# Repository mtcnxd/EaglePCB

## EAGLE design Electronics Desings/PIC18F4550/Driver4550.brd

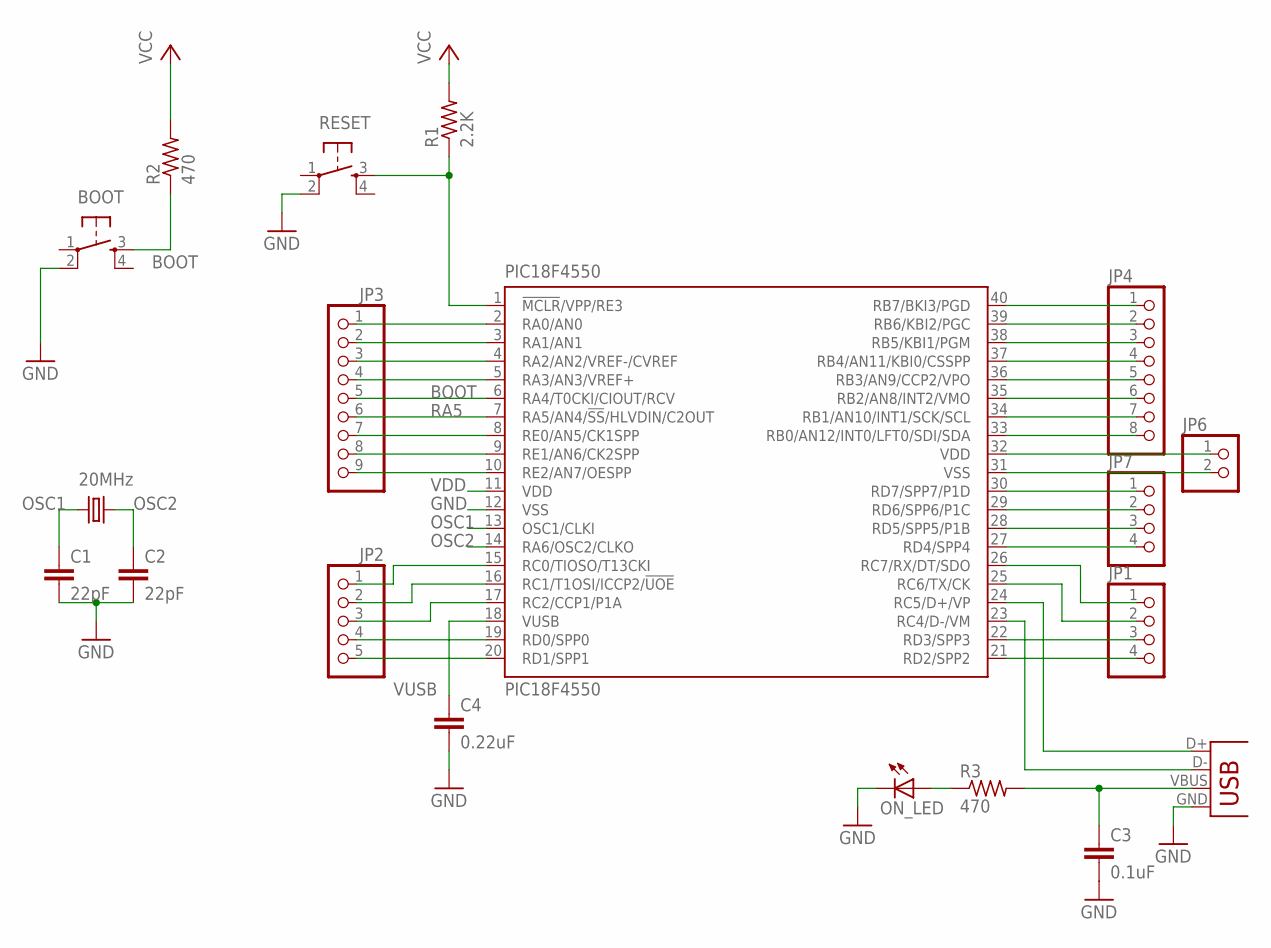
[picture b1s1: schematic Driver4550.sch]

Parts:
BOOT: TAC_SWITCHPTH; TACTILE-PTH
C1, C2: 22pF; C5B3
C3: 0.1uF; C2.5-3
C4: 0.22uF; C5B3
CRYSTAL: 20MHz; HC49US
JP1, JP7: PINHD-1X4; 1X04
JP2: PINHD-1X5; 1X05
JP3: PINHD-1X9; 1X09
JP4: PINHD-1X8; 1X08
JP6: PINHD-1X2; 1X02
ON_LED: LED3MM
PIC18F4550: PIC18F4550; DIL40
R1: 2.2K; 0204/7
R2, R3: 470; 0204/7
RESET: TAC_SWITCHPTH; TACTILE-PTH
USB: X1; USB-B-PTH

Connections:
B6: JP4.2, PIC18F4550.39 (RB6/KBI2/PGC)
B7: JP4.1, PIC18F4550.40 (RB7/BKI3/PGD)
BOOT: BOOT.3, JP3.5, PIC18F4550.6 (RA4/T0CKI/CIOUT/RCV), R2.1
D0: JP2.4, PIC18F4550.19 (RD0/SPP0)
D1: JP2.5, PIC18F4550.20 (RD1/SPP1)
D2: JP1.4, PIC18F4550.21 (RD2/SPP2)
D4: JP7.4, PIC18F4550.27 (RD4/SPP4)
D5: JP7.3, PIC18F4550.28 (RD5/SPP5/P1B)
D6: JP7.2, PIC18F4550.29 (RD6/SPP6/P1C)
D7: JP7.1, PIC18F4550.30 (RD7/SPP7/P1D)
D+: PIC18F4550.24 (RC5/D+/VP), USB.D+
D-: PIC18F4550.23 (RC4/D-/VM), USB.D-
GND: BOOT.2, C1.2, C2.2, C3.2, C4.2, JP6.2, ON_LED.K (C), PIC18F4550.12 (VSS), PIC18F4550.31 (VSS), RESET.2, USB.GND
unnamed: JP1.3, PIC18F4550.22 (RD3/SPP3)
unnamed: JP2.1, PIC18F4550.15 (RC0/TIOSO/T13CKI)
unnamed: JP1.2, PIC18F4550.25 (RC6/TX/CK)
unnamed: JP1.1, PIC18F4550.26 (RC7/RX/DT/SDO)
unnamed: PIC18F4550.1 (!MCLR!/VPP/RE3), R1.1, RESET.3
unnamed: JP2.2, PIC18F4550.16 (RC1/T1OSI/ICCP2/!UOE)
unnamed: ON_LED.A, R3.1
unnamed: JP4.8, PIC18F4550.33 (RB0/AN12/INT0/LFT0/SDI/SDA)
unnamed: JP4.7, PIC18F4550.34 (RB1/AN10/INT1/SCK/SCL)
unnamed: JP4.6, PIC18F4550.35 (RB2/AN8/INT2/VMO)
unnamed: JP4.5, PIC18F4550.36 (RB3/AN9/CCP2/VPO)
unnamed: JP4.4, PIC18F4550.37 (RB4/AN11/KBI0/CSSPP)
unnamed: JP4.3, PIC18F4550.38 (RB5/KBI1/PGM)
unnamed: JP2.3, PIC18F4550.17 (RC2/CCP1/P1A)
unnamed: JP3.1, PIC18F4550.2 (RA0/AN0)
unnamed: JP3.2, PIC18F4550.3 (RA1/AN1)
unnamed: JP3.3, PIC18F4550.4 (RA2/AN2/VREF-/CVREF)
unnamed: JP3.4, PIC18F4550.5 (RA3/AN3/VREF+)
unnamed: JP3.7, PIC18F4550.8 (RE0/AN5/CK1SPP)
unnamed: JP3.8, PIC18F4550.9 (RE1/AN6/CK2SPP)
unnamed: JP3.9, PIC18F4550.10 (RE2/AN7/OESPP)
OSC1: C1.1, CRYSTAL.2, PIC18F4550.13 (OSC1/CLKI)
OSC2: C2.1, CRYSTAL.1, PIC18F4550.14 (RA6/OSC2/CLKO)
RA5: JP3.6, PIC18F4550.7 (RA5/AN4/!SS!/HLVDIN/C2OUT)
VDD: C3.1, JP6.1, PIC18F4550.11 (VDD), PIC18F4550.32 (VDD), R1.2, R2.2, R3.2, USB.VBUS
VUSB: C4.1, PIC18F4550.18 (VUSB)

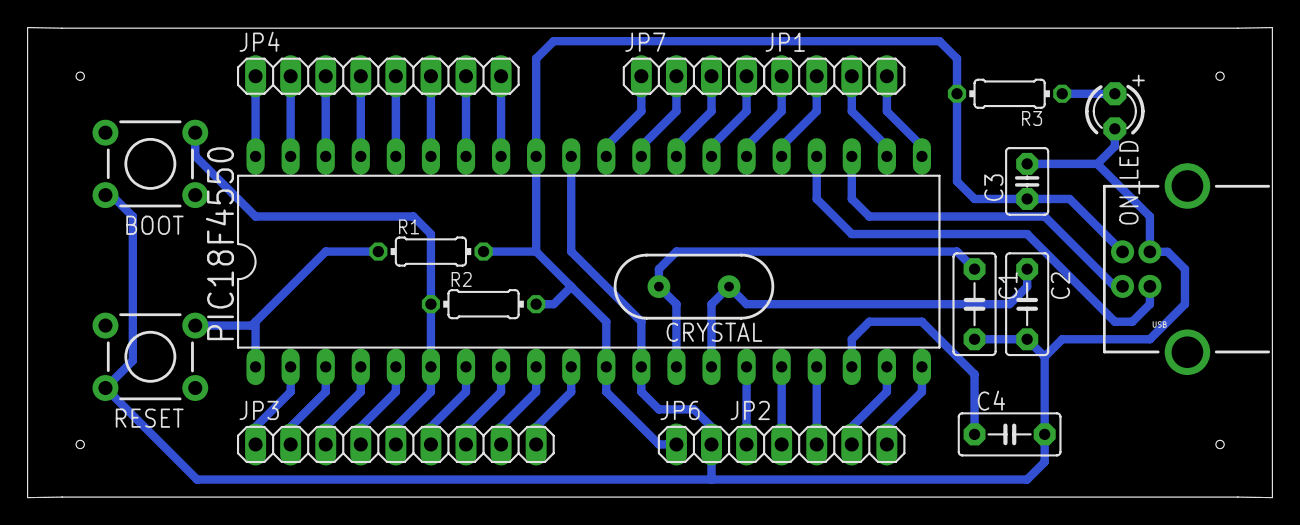
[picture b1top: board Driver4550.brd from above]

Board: 2 copper layers, 90.2 x 34.0 mm, 19 parts (0 on the bottom side), 39 nets.

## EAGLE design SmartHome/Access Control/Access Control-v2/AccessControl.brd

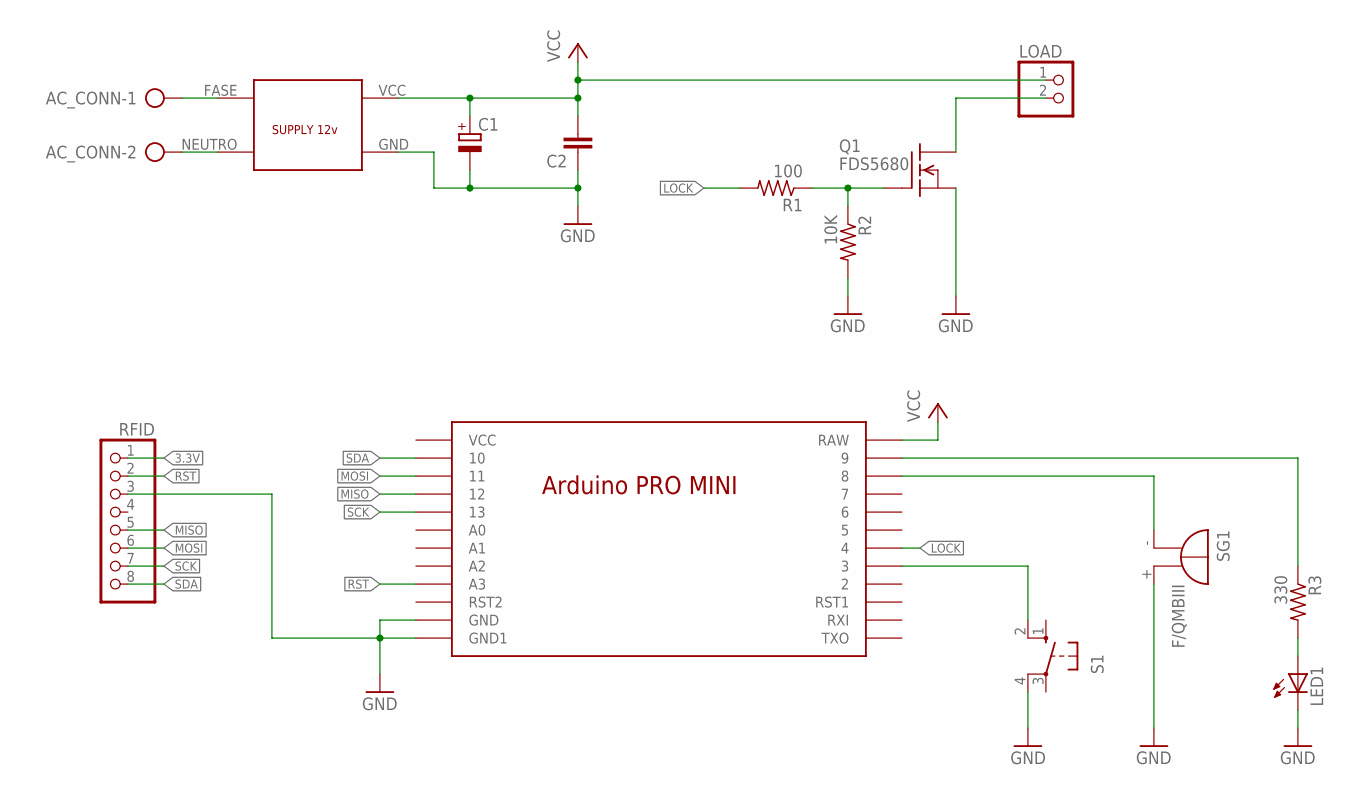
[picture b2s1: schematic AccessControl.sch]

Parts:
AC_CONN: AK300/2
C1: CPOL-EUE2.5-6; E2,5-6
C2: C2.5/2; C2.5-2
LED1: LED3MM
LOAD: PINHD-1X2; 1X02
Q1: FDS5680; SO-8
R1: 100; 0204/7
R2: 10K; 0204/7
R3: 330; 0204/7
RFID: PINHD-1X8; 1X08
S1: 10-XX; B3F-10XX
SG1: F/QMBIII
U$1: NANO
U$2: SUPPLY12V

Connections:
3.3V: RFID.1
GND: C1.-, C2.1, LED1.K (C), Q1.1 (S), Q1.2 (S), Q1.3 (S), R2.2, RFID.3, S1.4 (P1), SG1.+ (-), U$1.GND1 (GND), U$1.GND2 (GND1), U$2.GND
LOCK: R1.2, U$1.4
MISO: RFID.5, U$1.12
MOSI: RFID.6, U$1.11
unnamed: Q1.4 (G), R1.1, R2.1
unnamed: AC_CONN.2, U$2.NEUTRO
unnamed: LOAD.2, Q1.5 (D), Q1.6 (D), Q1.7 (D), Q1.8 (D)
unnamed: LED1.A, R3.2
unnamed: AC_CONN.1, U$2.FASE
unnamed: SG1.- (+), U$1.8
unnamed: S1.2 (S1), U$1.3
unnamed: R3.1, U$1.9
RST: RFID.2, U$1.A3
SCK: RFID.7, U$1.13
SDA: RFID.8, U$1.10
VCC: C1.+, C2.2, LOAD.1, U$1.RAW, U$2.VCC

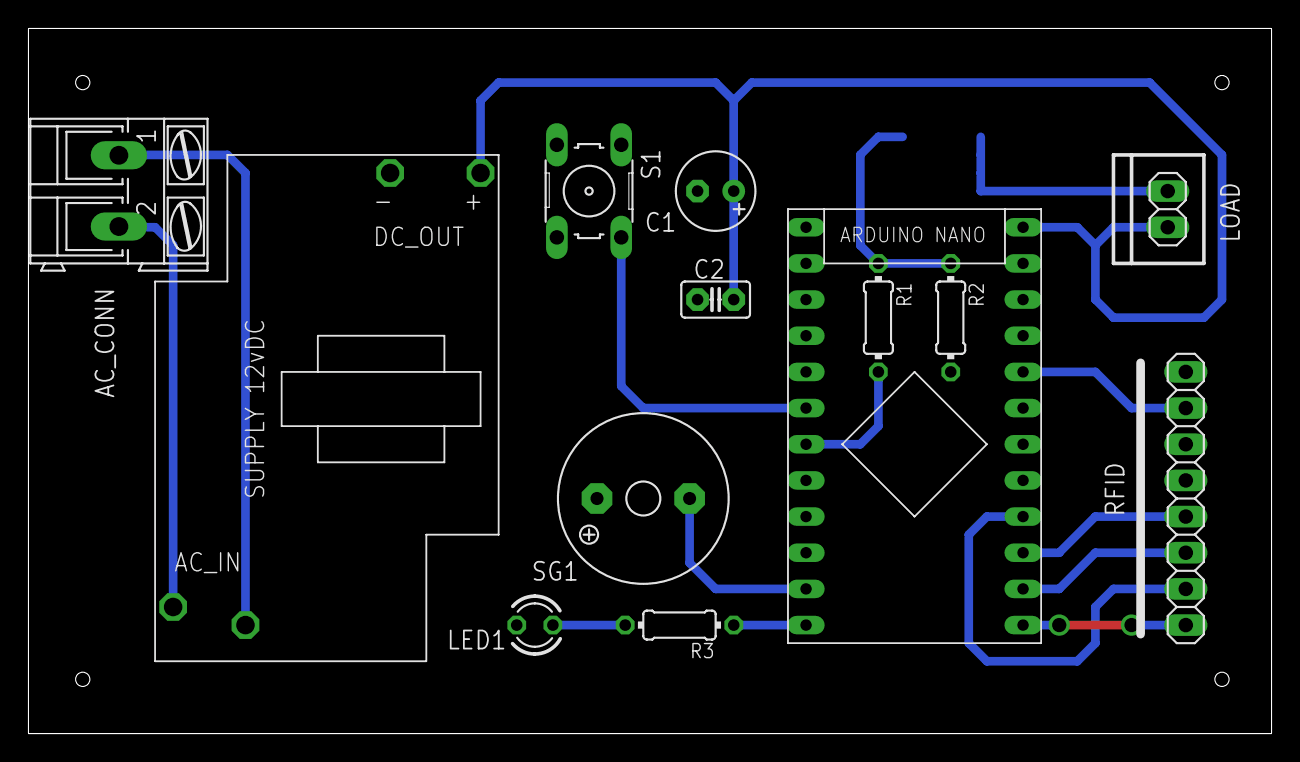
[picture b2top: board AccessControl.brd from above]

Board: 2 copper layers, 87.3 x 49.5 mm, 14 parts (1 on the bottom side), 16 nets.

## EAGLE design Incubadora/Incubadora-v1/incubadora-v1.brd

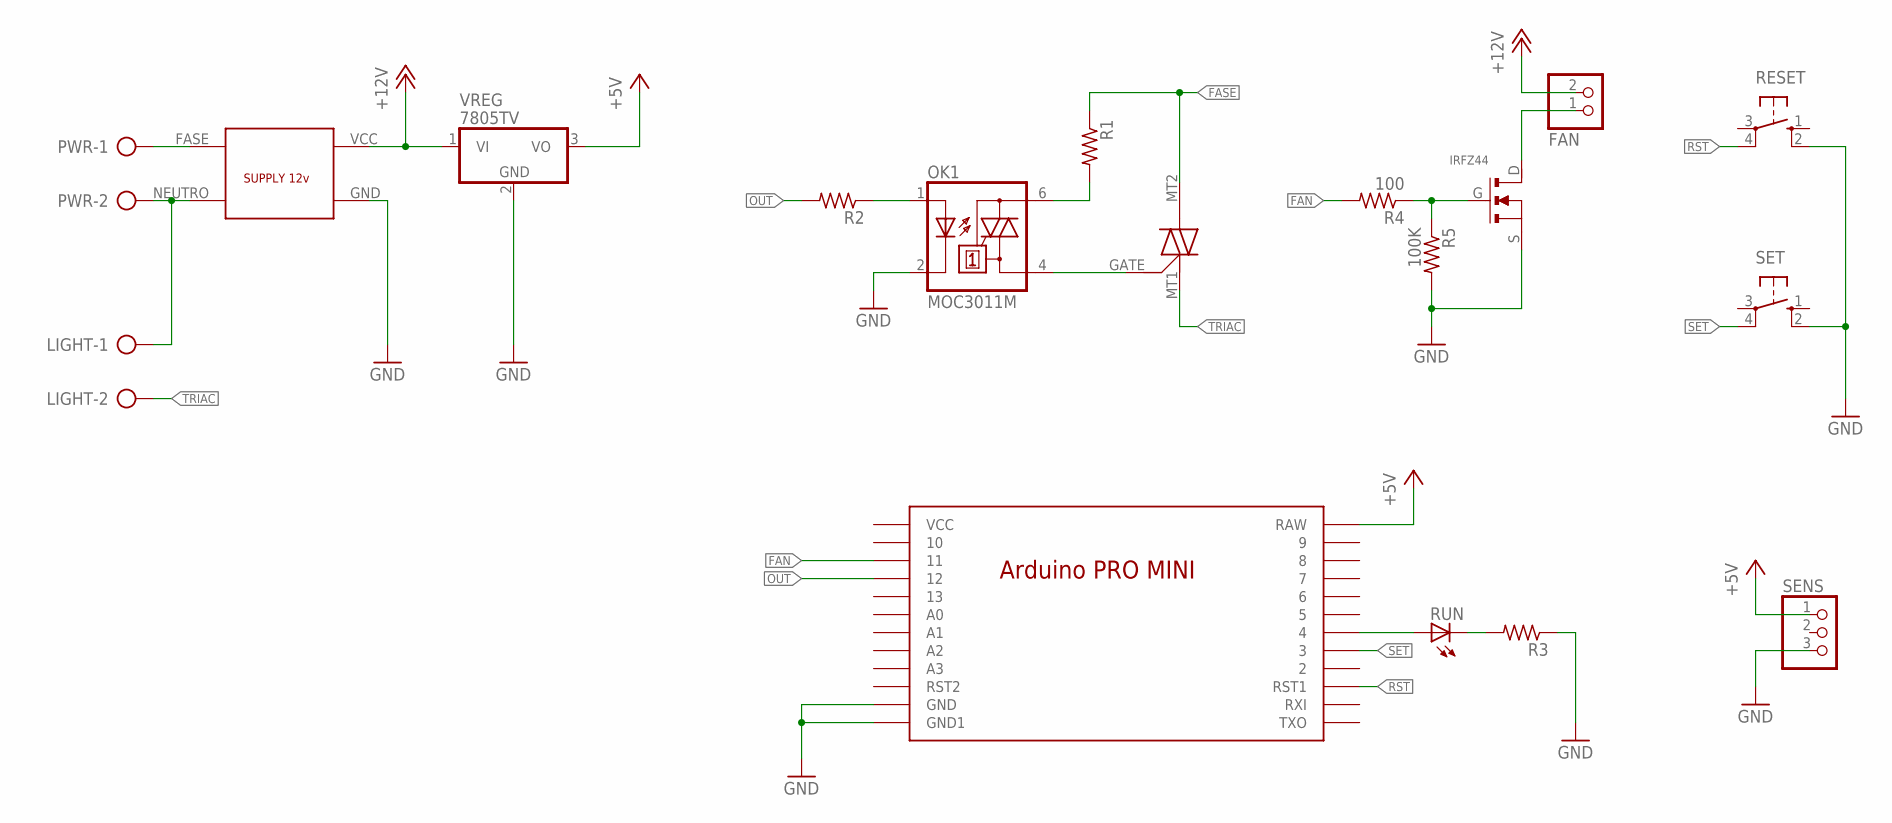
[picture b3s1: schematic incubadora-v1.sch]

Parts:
FAN: PINHD-1X2/90; 1X02/90
IRFZ44: IRFZ44
LIGHT: AK300/2
OK1: MOC3011M; DIL06
PWR: AK300/2
R1, R2, R3: R-US_0204/7; 0204/7
R4: 100; 0204/7
R5: 100K; 0204/7
RESET: 10-XX; B3F-10XX
RUN: LED5MM
SENS: PINHD-1X3/90; 1X03/90
SET: 10-XX; B3F-10XX
TRIAC: MAC12
U$1: NANO
U$3: SUPPLY12V
VREG: 7805TV; TO220V

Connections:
+5V: SENS.1, U$1.RAW, VREG.3 (VO)
+12V: FAN.2, U$3.VCC, VREG.1 (VI)
FAN: R4.2, U$1.11
FASE: PWR.1, R1.1, TRIAC.MT2, U$3.FASE
GND: IRFZ44.S, OK1.2 (C), R3.1, R5.2, RESET.2 (S1), SENS.3, SET.2 (S1), U$1.GND1 (GND), U$1.GND2 (GND1), U$3.GND, VREG.2 (GND)
unnamed: RUN.A, U$1.4
unnamed: OK1.1 (A), R2.1
unnamed: R3.2, RUN.K (C)
unnamed: LIGHT.1, PWR.2, U$3.NEUTRO
unnamed: OK1.6 (A2), R1.2
unnamed: IRFZ44.G, R4.1, R5.1
unnamed: FAN.1, IRFZ44.D
unnamed: OK1.4 (A1), TRIAC.GATE
OUT: R2.2, U$1.12
RST: RESET.4 (P1), U$1.RST1
SET: SET.4 (P1), U$1.3
TRIAC: LIGHT.2, TRIAC.MT1

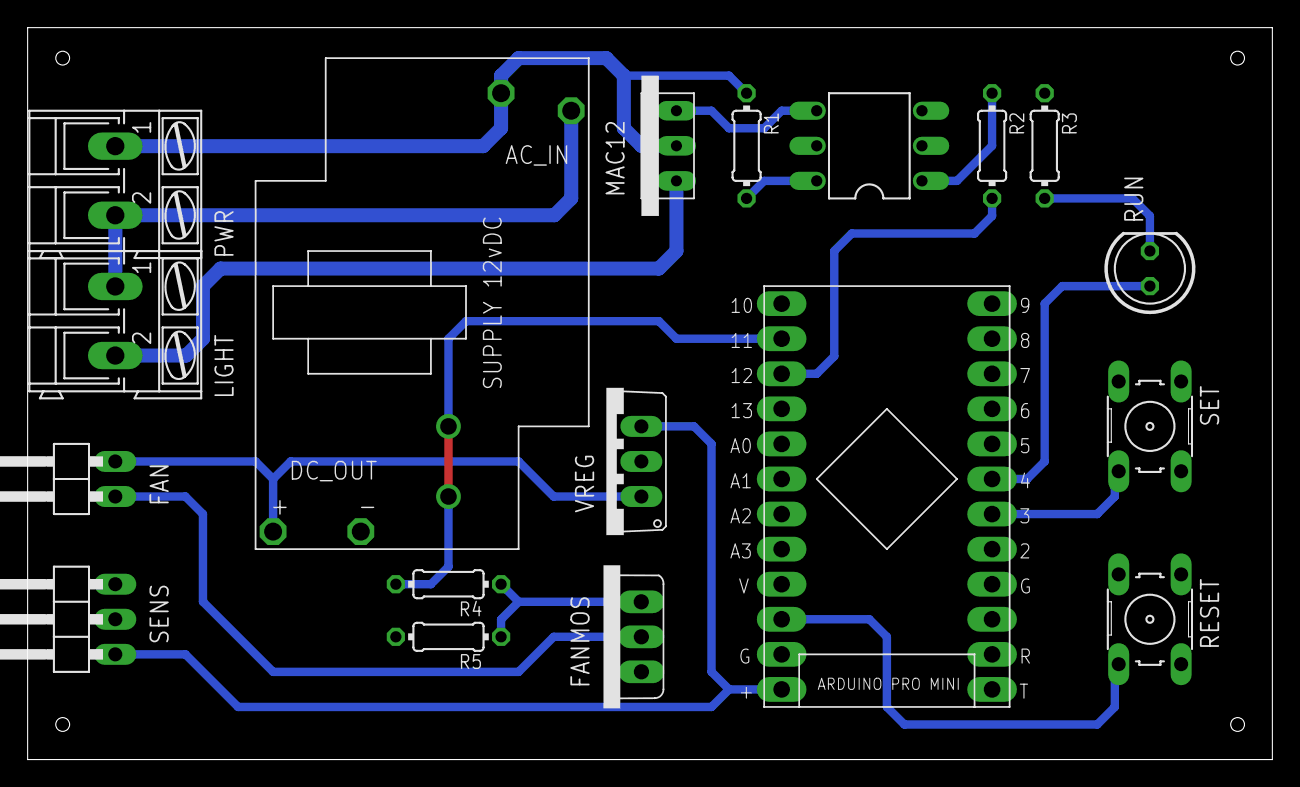
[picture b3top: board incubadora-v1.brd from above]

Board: 2 copper layers, 90.2 x 53.0 mm, 18 parts (0 on the bottom side), 17 nets.

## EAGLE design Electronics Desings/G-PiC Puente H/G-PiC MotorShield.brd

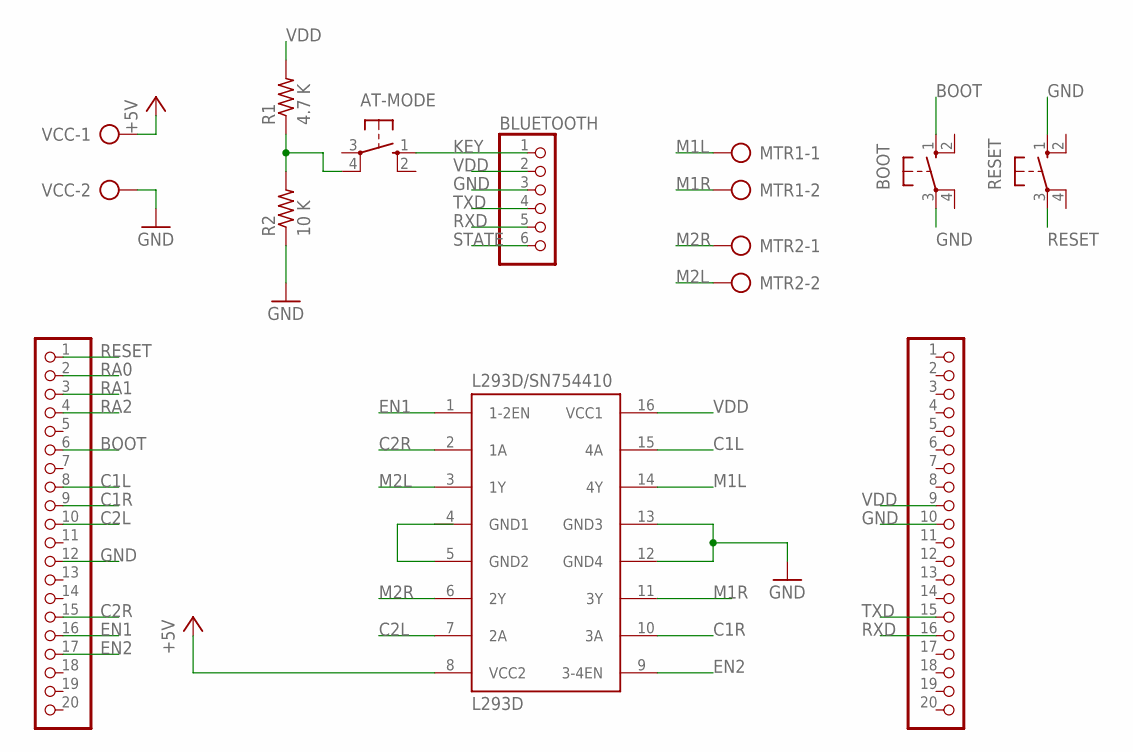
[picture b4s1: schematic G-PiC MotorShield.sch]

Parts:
AT-MODE: 10-XX; B3F-10XX; MPN B3F-1000
BLUETOOTH: PINHD-1X6; 1X06
BOOT: 10-XX; B3F-10XX
JP1, JP2: PINHD-1X20; 1X20
L293D/SN754410: L293D; DIL16
MTR1, MTR2: AK300/2
R1: 4.7 K; 0204/7
R2: 10 K; 0204/7
RESET: 10-XX; B3F-10XX; MPN B3F-1000
VCC: AK300/2

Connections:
+5V: L293D/SN754410.8 (VCC2), VCC.1
BOOT: BOOT.1 (S), JP2.6
C1L: JP2.8, L293D/SN754410.15 (4A)
C1R: JP2.9, L293D/SN754410.10 (3A)
C2L: JP2.10, L293D/SN754410.7 (2A)
C2R: JP2.15, L293D/SN754410.2 (1A)
EN1: JP2.16, L293D/SN754410.1 (1-2EN)
EN2: JP2.17, L293D/SN754410.9 (3-4EN)
GND: BLUETOOTH.3, BOOT.3, JP1.10, JP2.12, L293D/SN754410.12 (GND4), L293D/SN754410.13 (GND3), R2.1, RESET.1 (S), VCC.2
KEY: AT-MODE.4 (P1), R1.1, R2.2
M1L: L293D/SN754410.14 (4Y), MTR1.1
M1R: L293D/SN754410.11 (3Y), MTR1.2
M2L: L293D/SN754410.3 (1Y), MTR2.2
M2R: L293D/SN754410.6 (2Y), MTR2.1
unnamed: L293D/SN754410.4 (GND1), L293D/SN754410.5 (GND2)
unnamed: AT-MODE.1 (S), BLUETOOTH.1
RA0: JP2.2
RA1: JP2.3
RA2: JP2.4
RESET: JP2.1, RESET.3
RXD: BLUETOOTH.5, JP1.16
STATE: BLUETOOTH.6
TXD: BLUETOOTH.4, JP1.15
VDD: BLUETOOTH.2, JP1.9, L293D/SN754410.16 (VCC1), R1.2

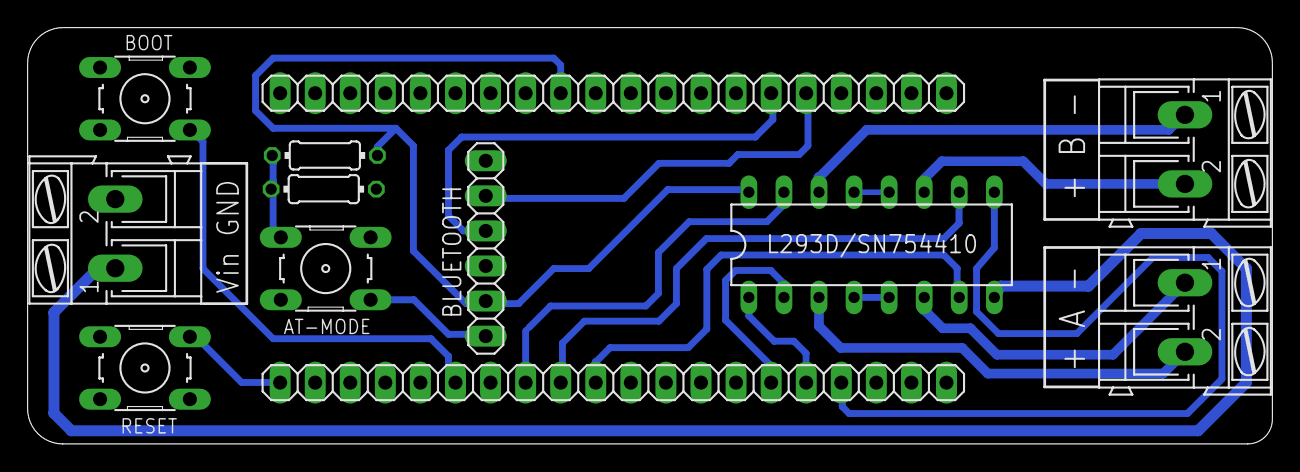
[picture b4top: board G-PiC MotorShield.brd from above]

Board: 2 copper layers, 90.2 x 30.1 mm, 12 parts (0 on the bottom side), 20 nets.

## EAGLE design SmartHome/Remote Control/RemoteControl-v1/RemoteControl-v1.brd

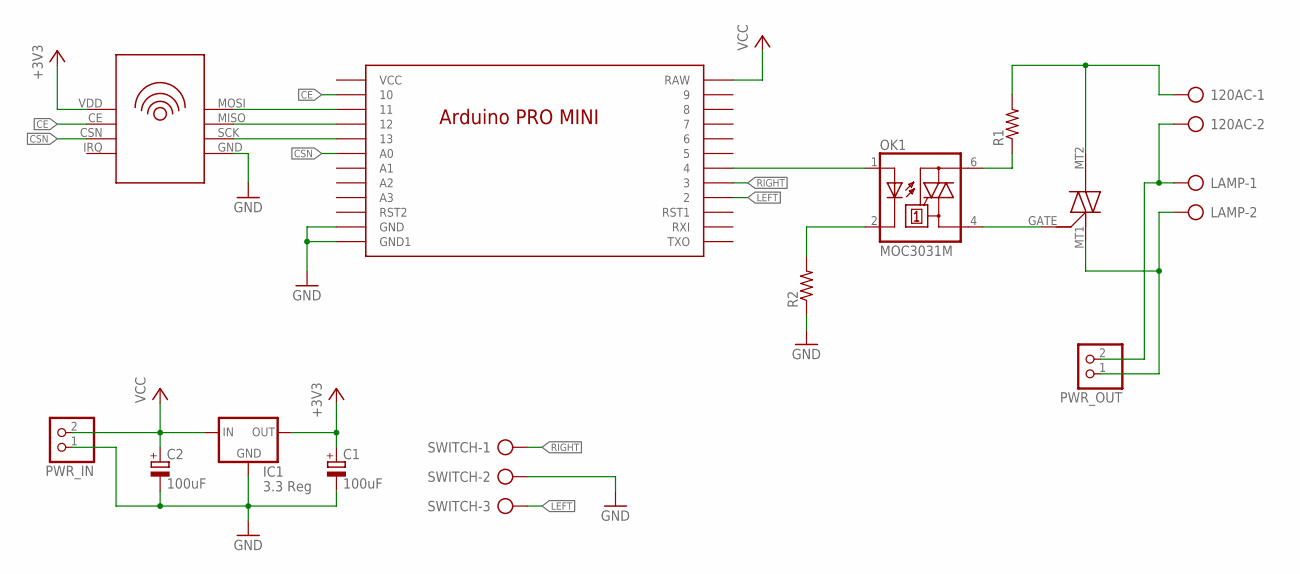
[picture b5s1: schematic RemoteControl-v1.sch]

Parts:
120AC: AK300/2
C1, C2: 100uF; E2,5-5
IC1: 3.3 Reg; 78LXX
LAMP: AK300/2
NRF24L01: NRF24L01
OK1: MOC3031M; DIL06
PWR_IN: PINHD-1X2; 1X02
PWR_OUT: PINHD-1X2; 1X02
R1, R2: R-US_0204/7; 0204/7
SWITCH: AK300/3
U$1: NANO
U$2: MAC12

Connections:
+3V3: C1.+, IC1.OUT, NRF24L01.VDD
CE: NRF24L01.CE, U$1.10
CSN: NRF24L01.CSN, U$1.A0
GND: C1.-, C2.-, IC1.GND, NRF24L01.GND, PWR_IN.1, R2.1, SWITCH.2, U$1.GND1 (GND), U$1.GND2 (GND1)
LEFT: SWITCH.3, U$1.2
unnamed: NRF24L01.SCK, U$1.13
unnamed: NRF24L01.MISO, U$1.12
unnamed: NRF24L01.MOSI, U$1.11
unnamed: OK1.6 (A2), R1.1
unnamed: LAMP.2, PWR_OUT.1, U$2.MT1
unnamed: 120AC.2, LAMP.1, PWR_OUT.2
unnamed: 120AC.1, R1.2, U$2.MT2
unnamed: OK1.2 (C), R2.2
unnamed: OK1.4 (A1), U$2.GATE
unnamed: OK1.1 (A), U$1.4
RIGHT: SWITCH.1, U$1.3
VCC: C2.+, IC1.IN, PWR_IN.2, U$1.RAW

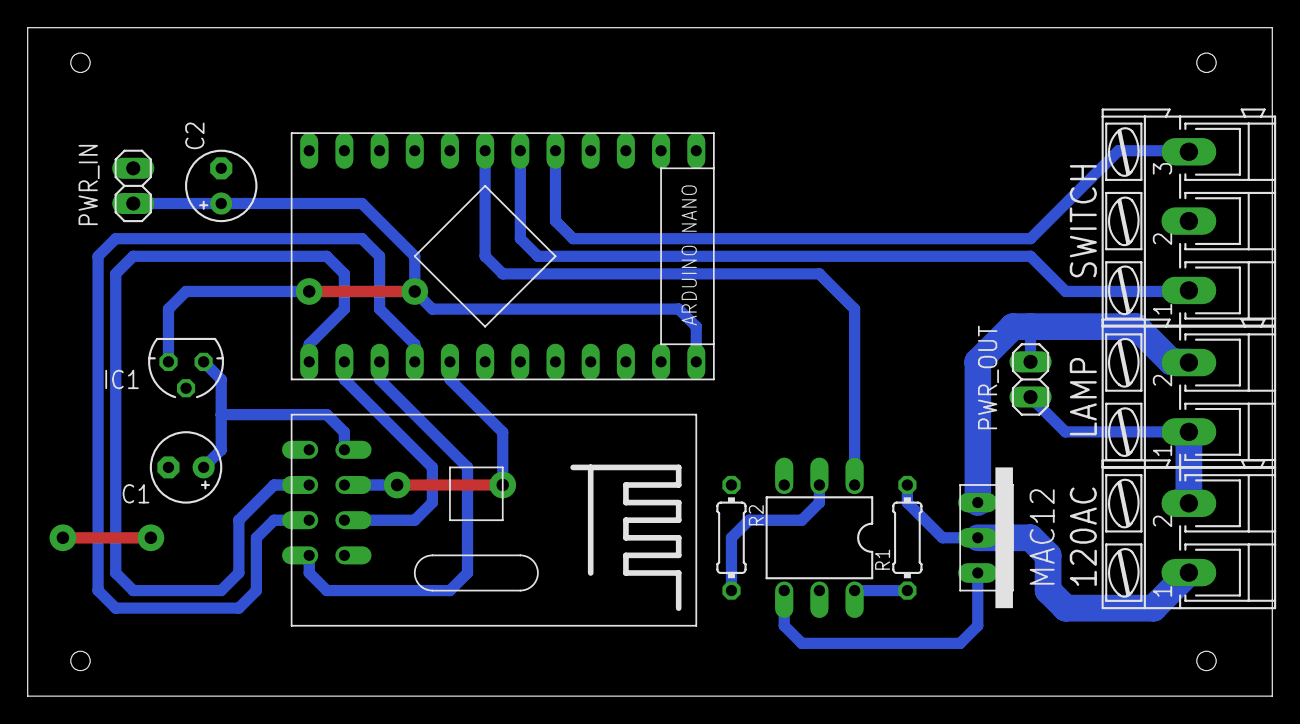
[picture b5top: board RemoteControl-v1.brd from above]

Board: 2 copper layers, 89.8 x 48.2 mm, 14 parts (0 on the bottom side), 17 nets.

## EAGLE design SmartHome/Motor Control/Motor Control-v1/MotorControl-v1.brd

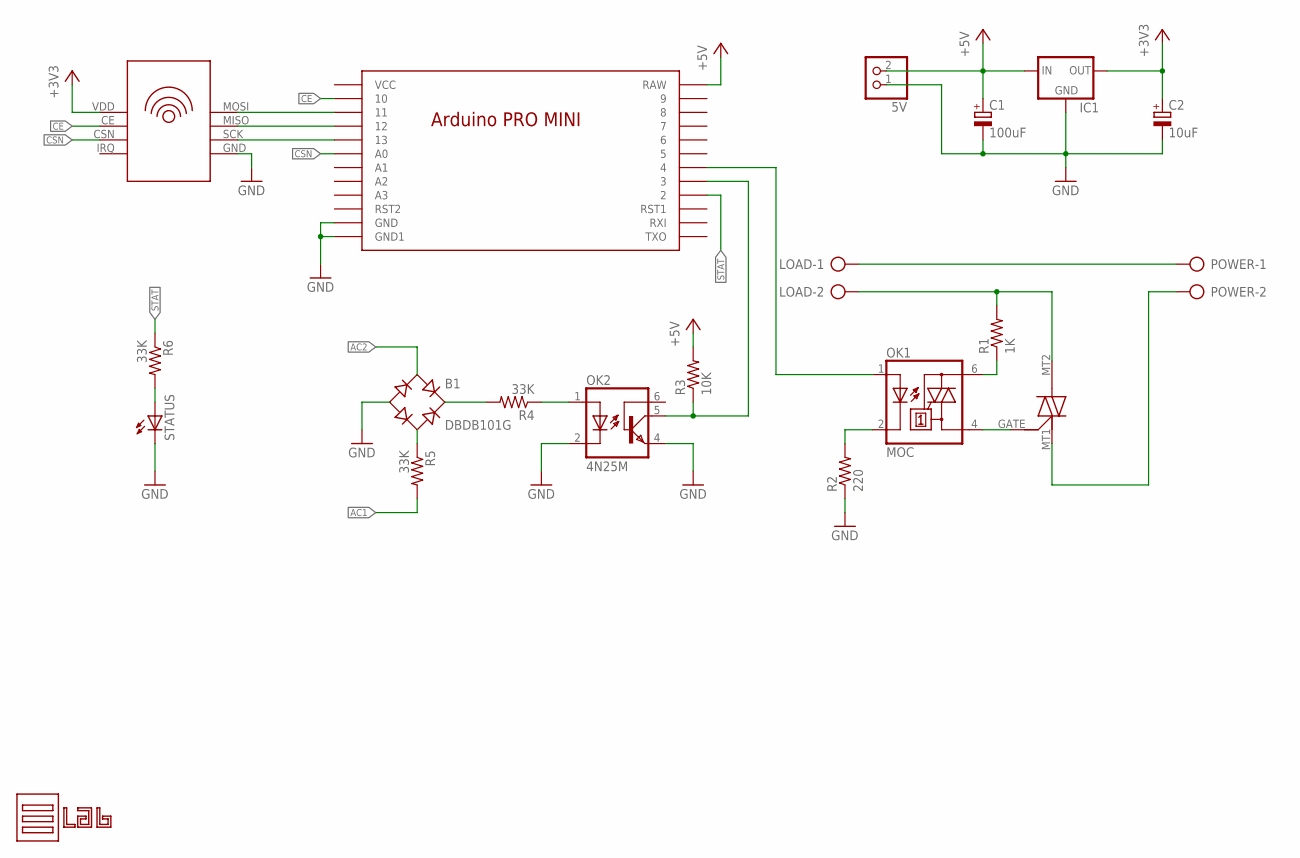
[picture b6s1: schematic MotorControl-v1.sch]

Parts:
5V: PINHD-1X2; 1X02
B1: DBDB101G; DB
C1: 100uF; E2-5
C2: 10uF; E2-5
IC1: 78LXX
J1: MAC12
LOAD: AK300/2
OK1: MOC; DIL06
OK2: 4N25M; DIL06
POWER: AK300/2
R1: 1K; 0204/7
R2: 220; 0204/7
R3: 10K; 0204/7
R4, R5, R6: 33K; 0204/7
STATUS: LED3MM
U$1: NANO
U$2: NRF24L01
U$3: LOGO

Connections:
+3V3: C2.+, IC1.OUT, U$2.VDD
+5V: 5V.2, C1.+, IC1.IN, R3.2, U$1.RAW
AC1: J1.MT1, POWER.2, R5.2
AC2: B1.AC1, LOAD.1, POWER.1
CE: U$1.10, U$2.CE
CSN: U$1.A0, U$2.CSN
GND: 5V.1, B1.-, C1.-, C2.-, IC1.GND, OK2.2 (C), OK2.4 (EMI), R2.1, STATUS.K (C), U$1.GND1 (GND), U$1.GND2 (GND1), U$2.GND
unnamed: J1.GATE, OK1.4 (A1)
unnamed: B1.AC2, R5.1
unnamed: OK1.1 (A), U$1.4
unnamed: U$1.13, U$2.SCK
unnamed: OK1.2 (C), R2.2
unnamed: OK1.6 (A2), R1.1
unnamed: OK2.5 (COL), R3.1, U$1.3
unnamed: B1.+, R4.2
unnamed: OK2.1 (A), R4.1
unnamed: U$1.12, U$2.MISO
unnamed: J1.MT2, LOAD.2, R1.2
unnamed: U$1.11, U$2.MOSI
unnamed: R6.2, STATUS.A
STAT: R6.1, U$1.2

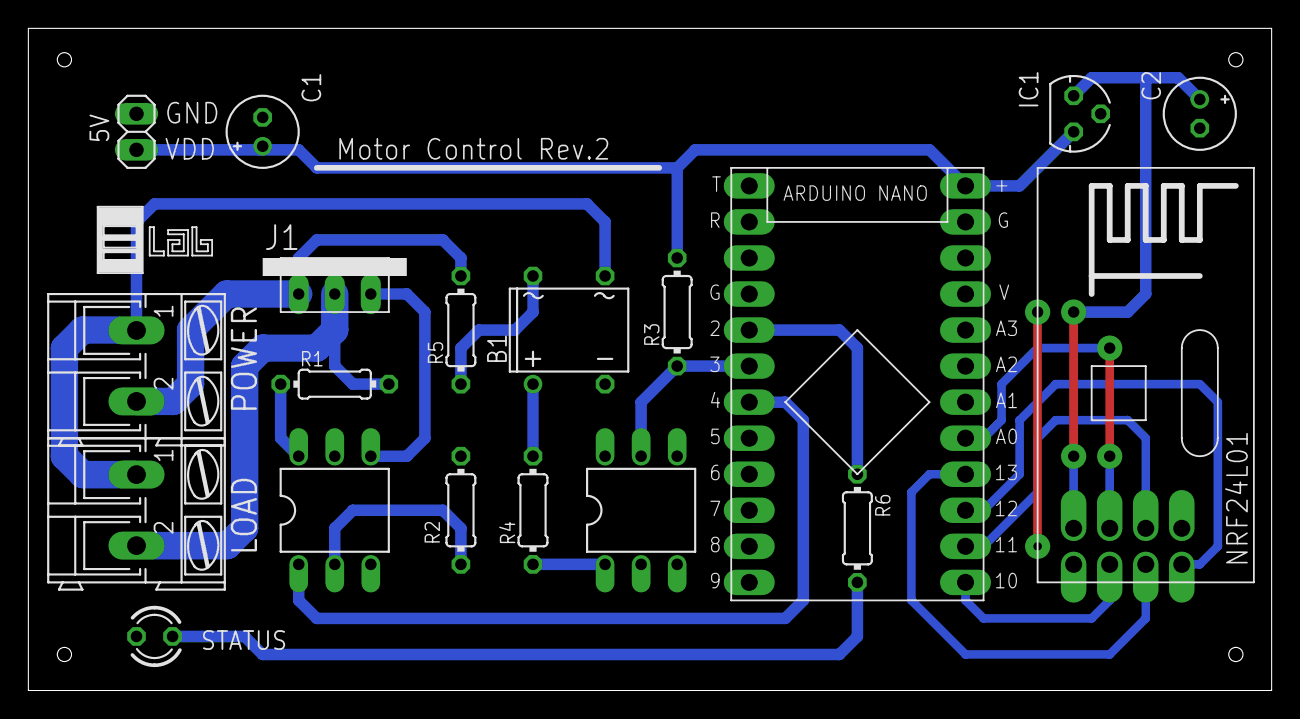
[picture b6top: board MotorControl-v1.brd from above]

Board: 2 copper layers, 87.6 x 46.7 mm, 20 parts (0 on the bottom side), 21 nets.

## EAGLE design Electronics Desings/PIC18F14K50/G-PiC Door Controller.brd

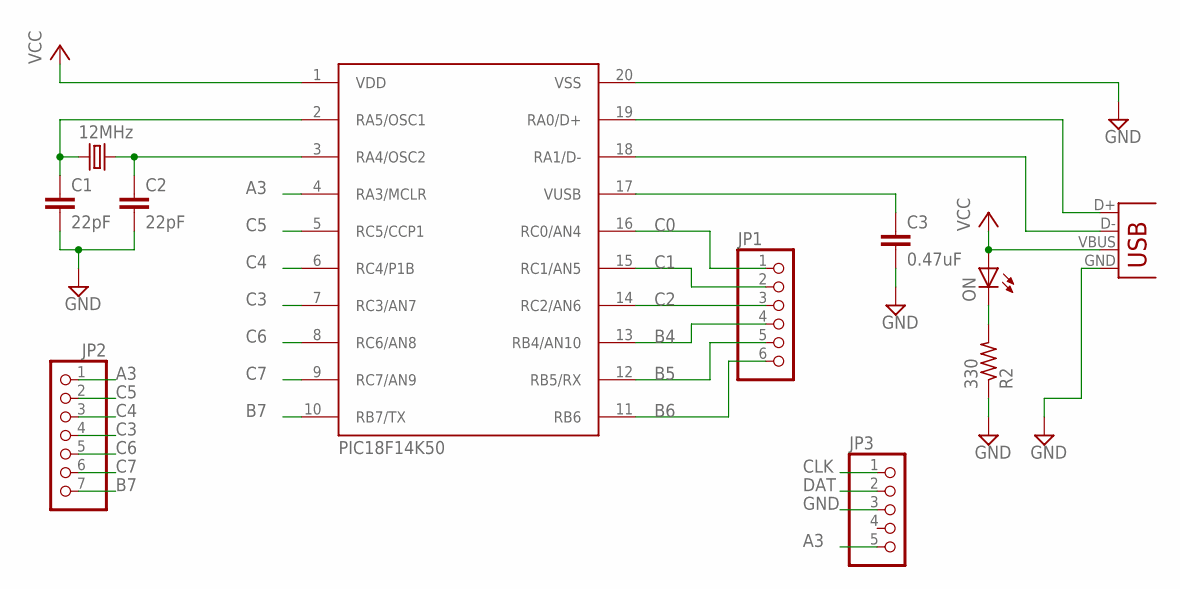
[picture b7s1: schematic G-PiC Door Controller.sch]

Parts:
C1, C2: 22pF; C5B3
C3: 0.47uF; C5B3
JP1: PINHD-1X6; 1X06
JP2: PINHD-1X7; 1X07
JP3: PINHD-1X5; 1X05
ON: LED3MM
PIC18F14K50: PIC18F14K50; DIL20
R2: 330; 0204/7
X3: USBPTH; USB-B-PTH
Y1: 12MHz; HC49US

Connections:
A3: JP2.1, JP3.5, PIC18F14K50.4 (RA3/MCLR)
B4: JP1.4, PIC18F14K50.13 (RB4/AN10)
B5: JP1.5, PIC18F14K50.12 (RB5/RX)
B6: JP1.6, PIC18F14K50.11 (RB6)
B7: JP2.7, PIC18F14K50.10 (RB7/TX)
C0: JP1.1, PIC18F14K50.16 (RC0/AN4)
C1: JP1.2, PIC18F14K50.15 (RC1/AN5)
C2: JP1.3, PIC18F14K50.14 (RC2/AN6)
C3: JP2.4, PIC18F14K50.7 (RC3/AN7)
C4: JP2.3, PIC18F14K50.6 (RC4/P1B)
C5: JP2.2, PIC18F14K50.5 (RC5/CCP1)
C6: JP2.5, PIC18F14K50.8 (RC6/AN8)
C7: JP2.6, PIC18F14K50.9 (RC7/AN9)
CLK: JP3.1, PIC18F14K50.18 (RA1/D-), X3.D-
DAT: JP3.2, PIC18F14K50.19 (RA0/D+), X3.D+
GND: C1.2, C2.2, C3.2, JP3.3, PIC18F14K50.20 (VSS), R2.1, X3.GND
unnamed: ON.K (C), R2.2
unnamed: C2.1, PIC18F14K50.3 (RA4/OSC2), Y1.2
unnamed: C1.1, PIC18F14K50.2 (RA5/OSC1), Y1.1
unnamed: C3.1, PIC18F14K50.17 (VUSB)
VCC: ON.A, PIC18F14K50.1 (VDD), X3.VBUS

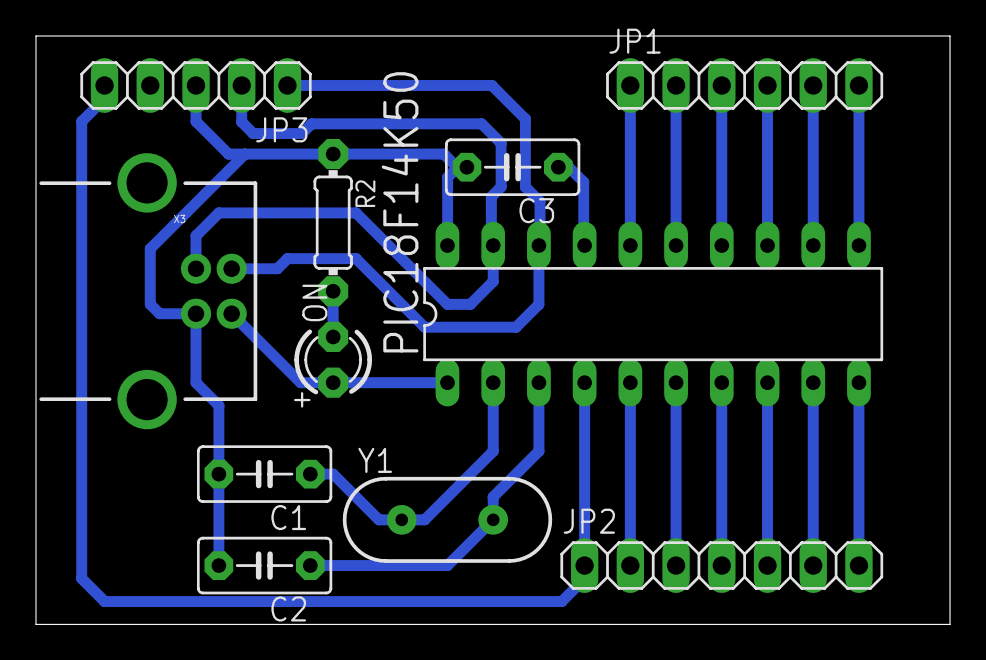
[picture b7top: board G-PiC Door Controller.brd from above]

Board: 2 copper layers, 50.8 x 32.7 mm, 11 parts (0 on the bottom side), 21 nets.

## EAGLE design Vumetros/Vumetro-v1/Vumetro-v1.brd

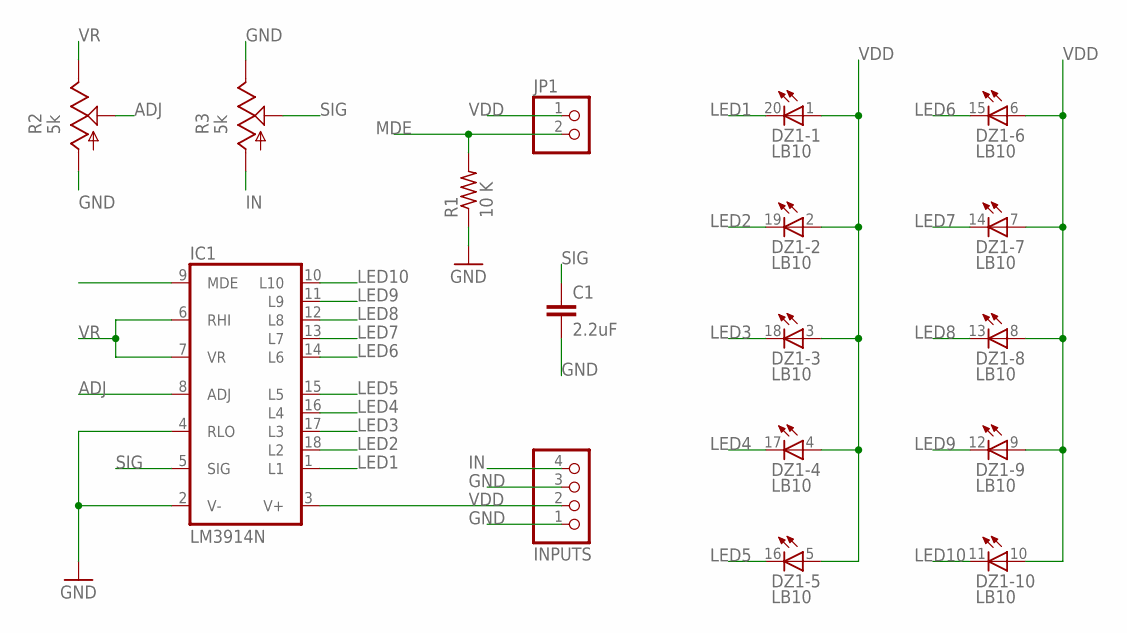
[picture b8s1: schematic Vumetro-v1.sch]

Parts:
C1: 2.2uF; C2.5-6
DZ1: LB10
IC1: LM3914N; DIL18
INPUTS: PINHD-1X4; 1X04
JP1: PINHD-1X2; 1X02
R1: 10 K; 0204/5
R2, R3: 5k; PT-10

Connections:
ADJ: IC1.8 (ADJ), R2.S
GND: C1.2, IC1.2 (V-), IC1.4 (RLO), INPUTS.1, INPUTS.3, R1.1, R2.A, R3.E
IN: INPUTS.4, R3.A
LED1: DZ1.20 (C), IC1.1 (L1)
LED2: DZ1.19 (C), IC1.18 (L2)
LED3: DZ1.18 (C), IC1.17 (L3)
LED4: DZ1.17 (C), IC1.16 (L4)
LED5: DZ1.16 (C), IC1.15 (L5)
LED6: DZ1.15 (C), IC1.14 (L6)
LED7: DZ1.14 (C), IC1.13 (L7)
LED8: DZ1.13 (C), IC1.12 (L8)
LED9: DZ1.12 (C), IC1.11 (L9)
LED10: DZ1.11 (C), IC1.10 (L10)
MDE: IC1.9 (MDE), JP1.2, R1.2
SIG: C1.1, IC1.5 (SIG), R3.S
VDD: DZ1.1 (A), DZ1.2 (A), DZ1.3 (A), DZ1.4 (A), DZ1.5 (A), DZ1.6 (A), DZ1.7 (A), DZ1.8 (A), DZ1.9 (A), DZ1.10 (A), IC1.3 (V+), INPUTS.2, JP1.1
VR: IC1.6 (RHI), IC1.7 (VR), R2.E

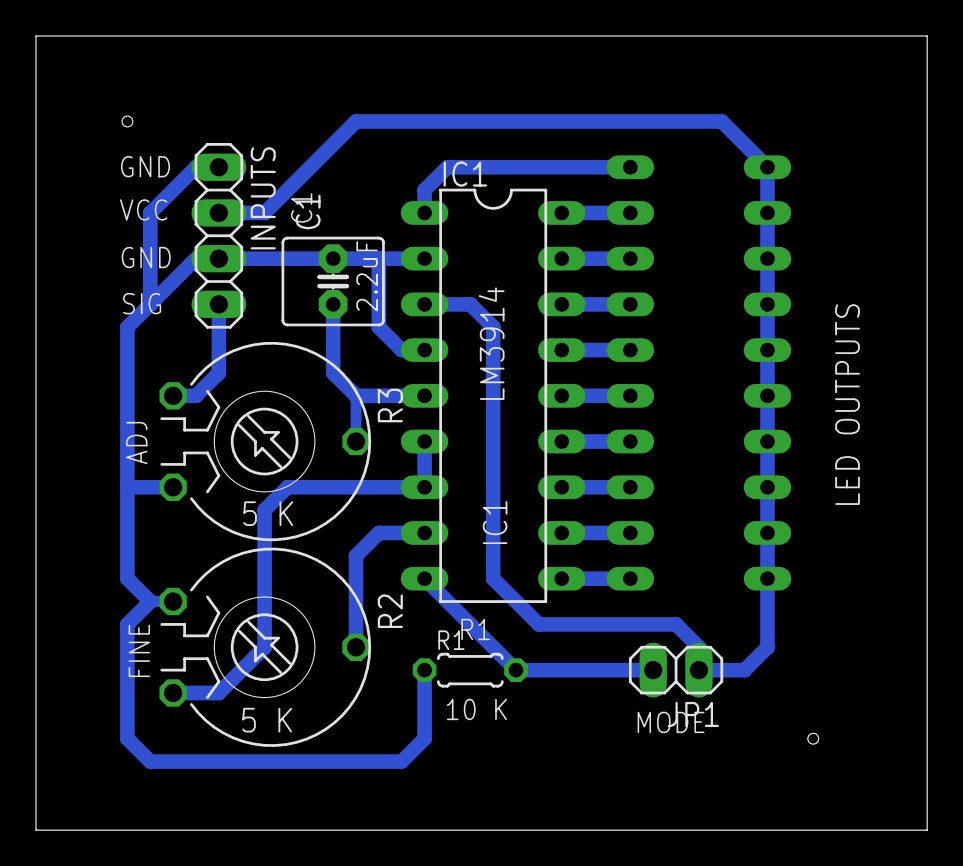
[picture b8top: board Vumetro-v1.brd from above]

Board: 2 copper layers, 49.5 x 44.1 mm, 8 parts (1 on the bottom side), 17 nets.

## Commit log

2022-01-14 Primeros archivos respaldados
2022-01-14 Respaldo de las placas elaboradas en Eagle
